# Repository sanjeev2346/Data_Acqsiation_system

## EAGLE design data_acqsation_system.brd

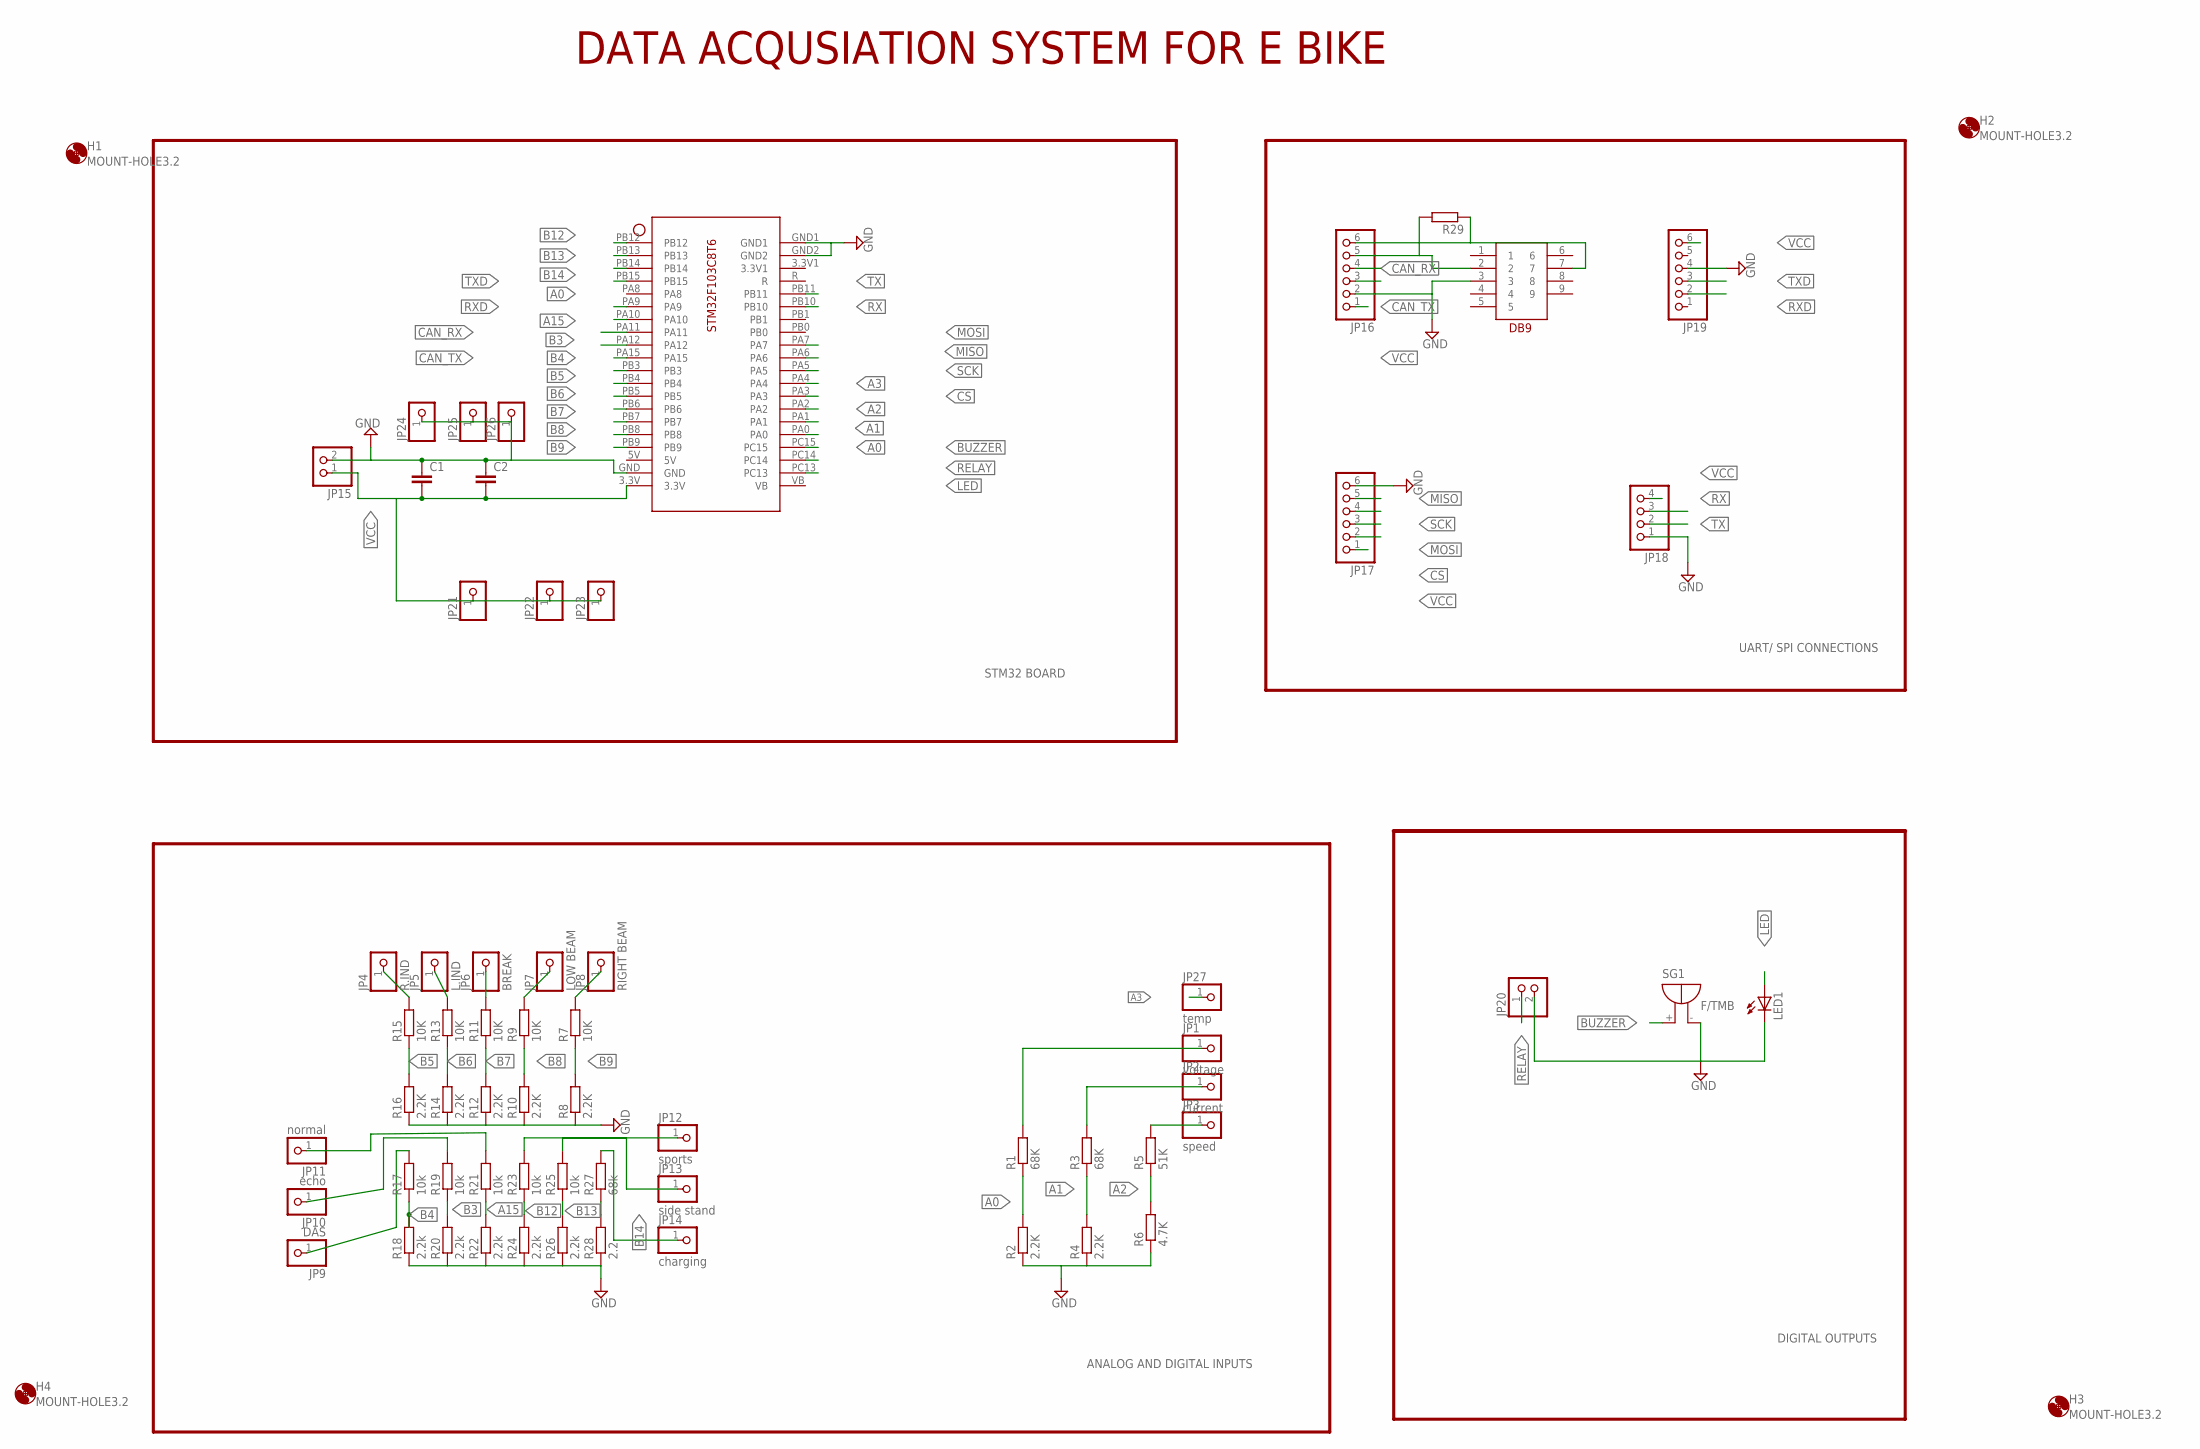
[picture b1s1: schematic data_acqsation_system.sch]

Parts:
C1, C2: C2.5/6; C2.5-6
H1, H2, H3, H4: MOUNT-HOLE3.2; 3,2
JP1: voltage; 1X01
JP2: current; 1X01
JP3: speed; 1X01
JP4: R.IND; 1X01
JP5: L.IND; 1X01
JP6: BREAK; 1X01
JP7: LOW BEAM; 1X01
JP8: RIGHT BEAM; 1X01
JP9: DAS; 1X01
JP10: echo; 1X01
JP11: normal; 1X01
JP12: sports; 1X01
JP13: side stand; 1X01
JP14: charging; 1X01
JP15, JP20: PINHD-1X2; 1X02
JP16, JP17, JP19: PINHD-1X6; 1X06
JP18: PINHD-1X4; 1X04
JP21, JP22, JP23, JP24, JP25, JP26: PINHD-1X1; 1X01
JP27: temp; 1X01
LED1: LED5MM
R1, R3: 68K; 0309/12
R2, R4, R8, R10, R12, R14, R16: 2.2K; 0309/12
R5: 51K; 0309/12
R6: 4.7K; 0309/12
R7, R9, R11, R13, R15: 10K; 0309/12
R17, R19, R21, R23, R25: 10k; 0309/12
R18, R20, R22, R24, R26: 2.2k; 0309/12
R27: 68k; 0309/12
R28: 2.2; 0309/12
R29: R-EU_0309/12; 0309/12
SG1: F/TMB
U$1: STM32F103C8T6
U$2: DB9

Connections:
A0: R1.1, R2.2, U$1.PA0, U$1.PB15
A1: R3.1, R4.2, U$1.PA1
A2: R5.1, R6.2, U$1.PA2
A3: JP27.1, U$1.PA4
A15: R21.1, R22.2, U$1.PA15
B3: R19.1, R20.2, U$1.PB3
B4: R17.1, R18.2, U$1.PB4
B5: R15.1, R16.2, U$1.PB5
B6: R13.1, R14.2, U$1.PB6
B7: R11.1, R12.2, U$1.PB7
B8: R9.1, R10.2, U$1.PB8
B9: R7.1, R8.2, U$1.PB9
B12: R23.1, R24.2, U$1.PB12
B13: R25.1, R26.2, U$1.PB13
B14: R27.1, R28.2, U$1.PB14
BUZZER: SG1.+, U$1.PC15
CAN_RX: JP16.4, U$1.PA11
CAN_TX: JP16.3, U$1.PA12
CS: JP17.2, U$1.PA3
GND: C1.1, C2.1, JP15.2, JP16.2, JP17.6, JP18.1, JP19.4, JP20.2, JP24.1, JP25.1, JP26.1, LED1.K (C), R2.1, R4.1, R6.1, R8.1, R10.1, R12.1, R14.1, R16.1, R18.1, R20.1, R22.1, R24.1, R26.1, R28.1, SG1.-, U$1.GND, U$1.GND1, U$1.GND2, U$2.3
LED: LED1.A, U$1.PC13
MISO: JP17.5, U$1.PA6
MOSI: JP17.3, U$1.PA7
unnamed: JP3.1, R5.2
unnamed: JP2.1, R3.2
unnamed: JP1.1, R1.2
unnamed: JP11.1, R21.2
unnamed: JP8.1, R7.2
unnamed: JP7.1, R9.2
unnamed: JP6.1, R11.2
unnamed: JP5.1, R13.2
unnamed: JP4.1, R15.2
unnamed: JP9.1, R17.2
unnamed: JP16.5, R29.2, U$2.2
unnamed: JP10.1, R19.2
unnamed: JP14.1, R27.2
unnamed: JP13.1, R25.2
unnamed: JP12.1, R23.2
unnamed: JP16.6, R29.1, U$2.7
RELAY: JP20.1, U$1.PC14
RX: JP18.3, U$1.PB10
RXD: JP19.2, U$1.PA10
SCK: JP17.4, U$1.PA5
TX: JP18.2, U$1.PB11
TXD: JP19.3, U$1.PA9
VCC: C1.2, C2.2, JP15.1, JP16.1, JP17.1, JP18.4, JP19.6, JP21.1, JP22.1, JP23.1, U$1.3.3V

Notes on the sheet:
STM32 BOARD
ANALOG AND DIGITAL INPUTS
DIGITAL OUTPUTS
UART/ SPI CONNECTIONS
DATA ACQUSIATION SYSTEM FOR E BIKE

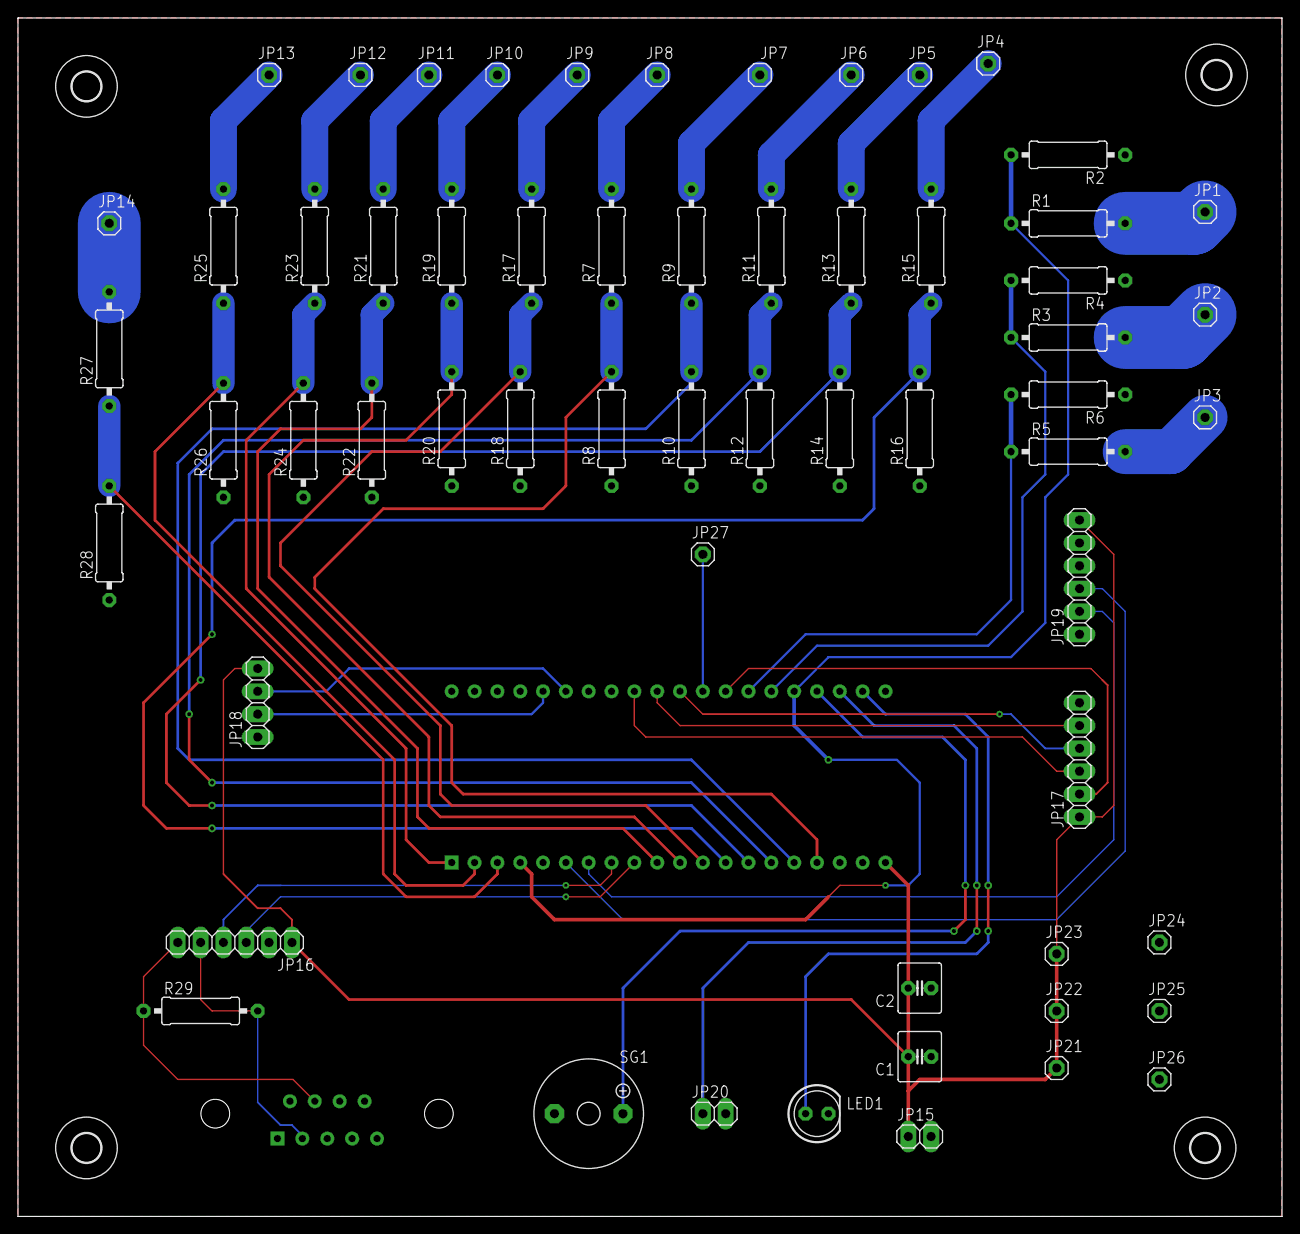
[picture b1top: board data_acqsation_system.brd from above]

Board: 2 copper layers, 140.6 x 133.3 mm, 66 parts (0 on the bottom side), 46 nets.

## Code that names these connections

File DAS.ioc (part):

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Mcu.Name=STM32F103C(8-B)Tx
Mcu.Package=LQFP48
Mcu.UserName=STM32F103C8Tx
PA0-WKUP.Signal=ADCx_IN0
PA1.Signal=ADCx_IN1
PA10.Mode=Asynchronous
PA10.Signal=USART1_RX
PA13.Mode=Serial_Wire
PA13.Signal=SYS_JTMS-SWDIO
PA14.Mode=Serial_Wire
PA14.Signal=SYS_JTCK-SWCLK
PA15.Signal=GPIO_Input
PA2.Signal=ADCx_IN2
PA3.Signal=GPIO_Output
PA4.Signal=ADCx_IN4
PA5.Mode=Full_Duplex_Master
PA5.Signal=SPI1_SCK
PA6.Mode=Full_Duplex_Master
PA6.Signal=SPI1_MISO
PA7.Mode=Full_Duplex_Master
PA7.Signal=SPI1_MOSI
PA8.Signal=GPIO_Input
PA9.Mode=Asynchronous
PA9.Signal=USART1_TX
PB10.Mode=Asynchronous
PB10.Signal=USART3_TX
PB11.Mode=Asynchronous
PB11.Signal=USART3_RX
PB12.Signal=GPIO_Input
PB13.Signal=GPIO_Input
PB14.Signal=GPIO_Input
PB15.Signal=GPIO_Input
PB3.Signal=GPIO_Input
PB4.Signal=GPIO_Input
PB5.Signal=GPIO_Input
PB6.Signal=GPIO_Input
PB7.Signal=GPIO_Input
PB8.Signal=GPIO_Input
PB9.Signal=GPIO_Input
PC13-TAMPER-RTC.Signal=GPIO_Output
PC14-OSC32_IN.Signal=GPIO_Output
PC15-OSC32_OUT.Signal=GPIO_Output
PD0-OSC_IN.Mode=HSE-External-Oscillator
PD0-OSC_IN.Signal=RCC_OSC_IN
PD1-OSC_OUT.Mode=HSE-External-Oscillator
PD1-OSC_OUT.Signal=RCC_OSC_OUT
RCC.SYSCLKFreq_VALUE=72000000
RCC.SYSCLKSource=RCC_SYSCLKSOURCE_PLLCLK
board=custom
